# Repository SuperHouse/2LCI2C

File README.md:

2 x Load Cell I2C Interface
===========================
Copyright 2020 SuperHouse Automation Pty Ltd <www.superhouse.tv>  
Designed by Jonathan Oxer

A pair of load cell amplifiers with an ATTiny84 microcontroller to
provide an I2C interface to the load cells.

Features:

 * 2 x load cell interfaces
 * I2C connection

More information is available at:

  http://www.superhouse.tv/2lci2c

INSTALLATION
------------
The design is saved as an EAGLE project. EAGLE PCB design software is
available from www.cadsoftusa.com free for non-commercial use. To use
this project download it and place the directory containing these files
into the "eagle" directory on your computer. Then open EAGLE and
navigate to the project.

DISTRIBUTION
------------
The specific terms of distribution of this project are governed by the
license referenced below.

LICENSE
-------
Licensed under the TAPR Open Hardware License (www.tapr.org/OHL).
The "license" folder within this repository also contains a copy of
this license in plain text format.

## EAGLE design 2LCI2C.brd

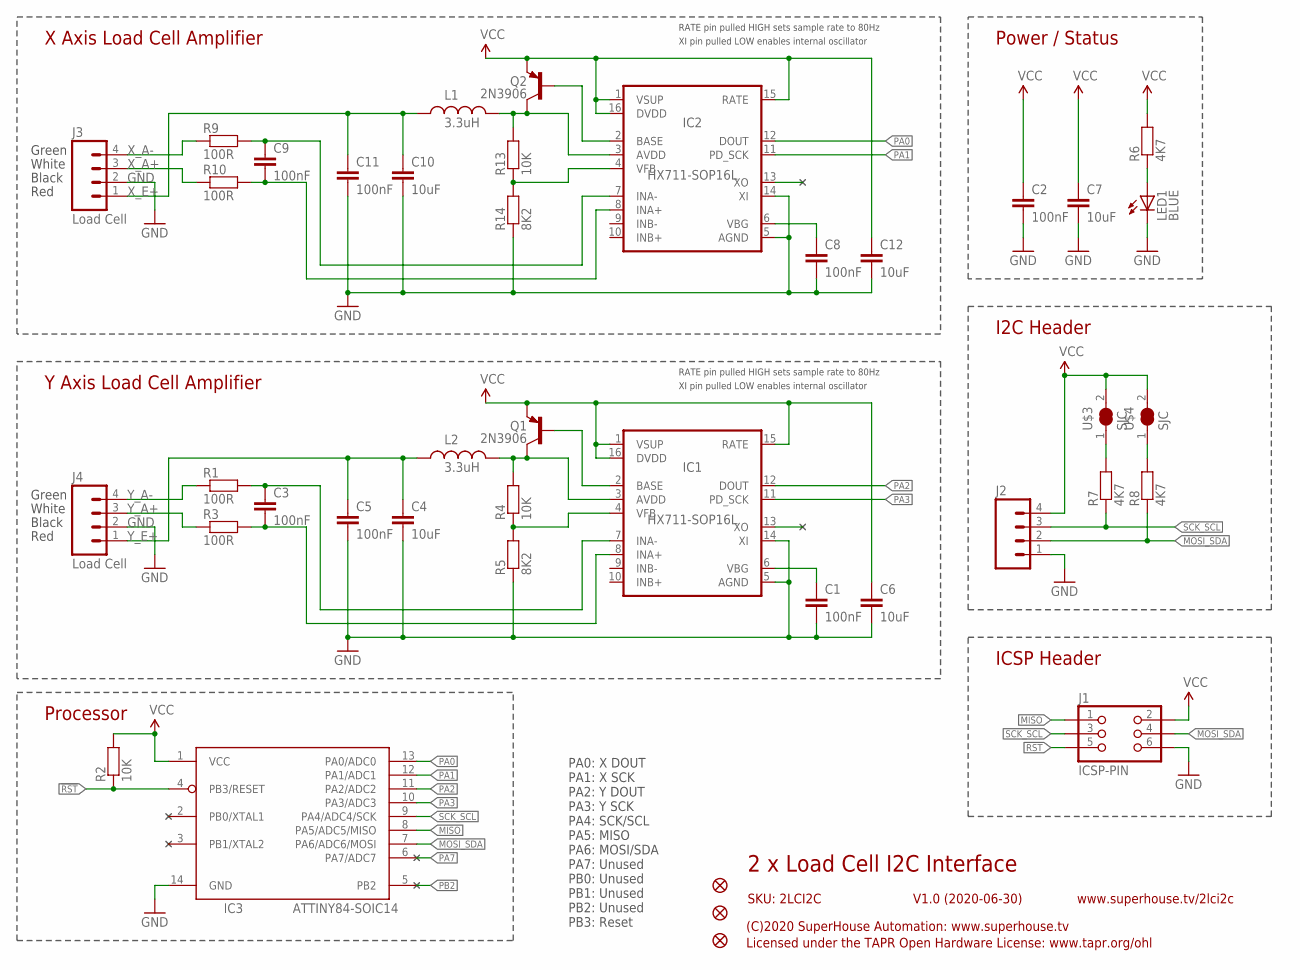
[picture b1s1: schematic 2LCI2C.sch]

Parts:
C1, C2, C3, C5, C8, C9, C11: 100nF; C0603
C4, C6, C7, C10, C12: 10uF; C0805
IC1, IC2: HX711-SOP16L; SOP16-L
IC3: ATTINY84-SOIC14; SOIC14
J1: ICSP-PIN; 2X03-ICSP
J2: M04-PLAIN; 1X04
J3, J4: Load Cell; 1X04-1.27-PLAIN
L1, L2: 3.3uH; L0603
LED1: BLUE; LED-0603
Q1, Q2: 2N3906; SOT23-BEC
R1, R3, R9, R10: 100R; R0603
R2, R4, R13: 10K; R0603
R5, R14: 8K2; R0603
R6, R7, R8: 4K7; R0603
U$3, U$4: SJC
U$5, U$10, U$11: FIDUCIAL1X2.5; FIDUCIAL-1X2.5

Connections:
!RST: IC3.4 (PB3/RESET), J1.5, R2.1
GND: C1.2, C2.2, C4.2, C5.2, C6.2, C7.2, C8.2, C10.2, C11.2, C12.2, IC1.5 (AGND), IC1.14 (XI), IC2.5 (AGND), IC2.14 (XI), IC3.14 (GND), J1.6, J2.1, J3.2, J4.2, LED1.C, R5.1, R14.1
MISO: IC3.8 (PA5/ADC5/MISO), J1.1
MOSI_SDA: IC3.7 (PA6/ADC6/MOSI), J1.4, J2.2, R8.1
unnamed: C3.1, IC1.7 (INA-), R1.2
unnamed: C3.2, IC1.8 (INA+), R3.2
unnamed: C1.1, IC1.6 (VBG)
unnamed: IC1.2 (BASE), Q1.B
unnamed: LED1.A, R6.1
unnamed: IC1.4 (VFB), R4.1, R5.2
unnamed: IC1.3 (AVDD), L2.2, Q1.C, R4.2
unnamed: R7.2, U$3.1
unnamed: R8.2, U$4.1
unnamed: C9.1, IC2.7 (INA-), R9.2
unnamed: C9.2, IC2.8 (INA+), R10.2
unnamed: IC2.3 (AVDD), L1.2, Q2.C, R13.2
unnamed: C8.1, IC2.6 (VBG)
unnamed: IC2.2 (BASE), Q2.B
unnamed: IC2.4 (VFB), R13.1, R14.2
PA0: IC2.12 (DOUT), IC3.13 (PA0/ADC0)
PA1: IC2.11 (PD_SCK), IC3.12 (PA1/ADC1)
PA2: IC1.12 (DOUT), IC3.11 (PA2/ADC2)
PA3: IC1.11 (PD_SCK), IC3.10 (PA3/ADC3)
PA7: IC3.6 (PA7/ADC7)
PB2: IC3.5 (PB2)
SCK_SCL: IC3.9 (PA4/ADC4/SCK), J1.3, J2.3, R7.1
VCC: C2.1, C6.1, C7.1, C12.1, IC1.1 (VSUP), IC1.15 (RATE), IC1.16 (DVDD), IC2.1 (VSUP), IC2.15 (RATE), IC2.16 (DVDD), IC3.1 (VCC), J1.2, J2.4, Q1.E, Q2.E, R2.2, R6.2, U$3.2, U$4.2
X_A+: J3.3, R10.1
X_A-: J3.4, R9.1
X_E+: C10.1, C11.1, J3.1, L1.1
Y_A+: J4.3, R3.1
Y_A-: J4.4, R1.1
Y_E+: C4.1, C5.1, J4.1, L2.1

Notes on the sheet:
2 x Load Cell I2C Interface
V1.0 (2020-06-30)
SKU: 2LCI2C
(C)2020 SuperHouse Automation: www.superhouse.tv
Licensed under the TAPR Open Hardware License: www.tapr.org/ohl
www.superhouse.tv/2lci2c
Power / Status
PA0: X DOUT PA1: X SCK PA2: Y DOUT PA3: Y SCK PA4: SCK/SCL PA5: MISO PA6: MOSI/SDA PA7: Unused PB0: Unused PB1: Unused PB2: Unused PB3: Reset
X Axis Load Cell Amplifier
RATE pin pulled HIGH sets sample rate to 80Hz
Y Axis Load Cell Amplifier
XI pin pulled LOW enables internal oscillator
I2C Header
Processor
ICSP Header
Red
Black
White
Green

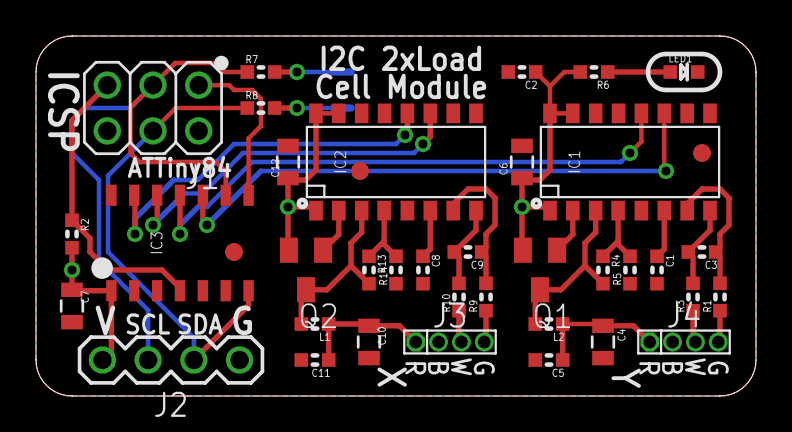
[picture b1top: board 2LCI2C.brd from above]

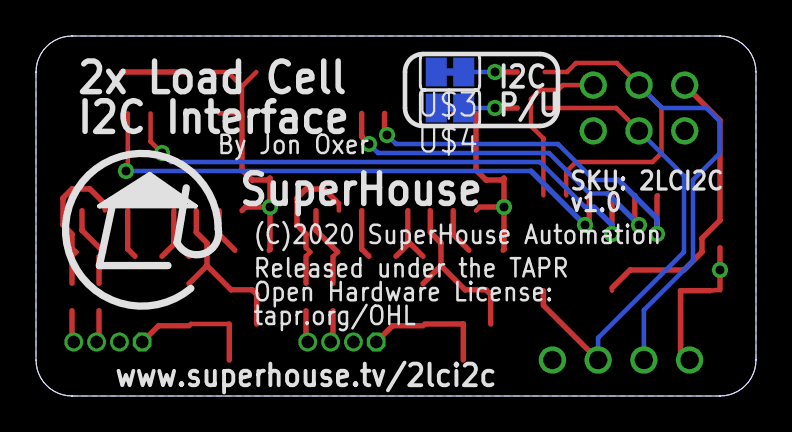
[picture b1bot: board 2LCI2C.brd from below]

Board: 2 copper layers, 40.0 x 20.0 mm, 41 parts (2 on the bottom side), 31 nets.

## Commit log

2020-06-30 Version 1.0 release
2020-07-02 Changed sample rate from 10Hz to 80Hz
2020-07-06 Added fiducials for re-release v1.0
2020-08-10 Layers
